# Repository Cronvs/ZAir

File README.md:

DISCLAIMER: The authors of this project are not responsible for how the files are used in any capacity.

CREDIT: This work is directly derivative of the work by [AirGradient](https://www.airgradient.com/)

BUGS: Molex picoblade connector to the "pms5003" is reversed. Cable thus need to be re-crimped, or need to reverse order between sensor and connection.

### ZAir
This work is directly compatible with the [AirGradient ONE](https://www.airgradient.com/indoor/),
it was created in frustration of the size over the monitor,
and personal opinions on LED, including but not limited to screens.

It is indeed a fork of the work done by AirGradient themselves, without whom this project would not have happened.
It was redesigned in KiCAD and has been verified in production via JLCPCB.

All sensors have been integrated directly into the main board, this removes superfluous board ordering or assembly,
however, it also means that "upgrading" with new sensors is harder.
The dimensions have approximately been halved, decreasing the area to around a quarter of the original design.
More could probably be done, but inexperience, and assumptions that the people at AirGradient probably had some good
reason except just temperature made the sensor into the size it is today.

If you like this project consider buying the author(s) a coffee or two.

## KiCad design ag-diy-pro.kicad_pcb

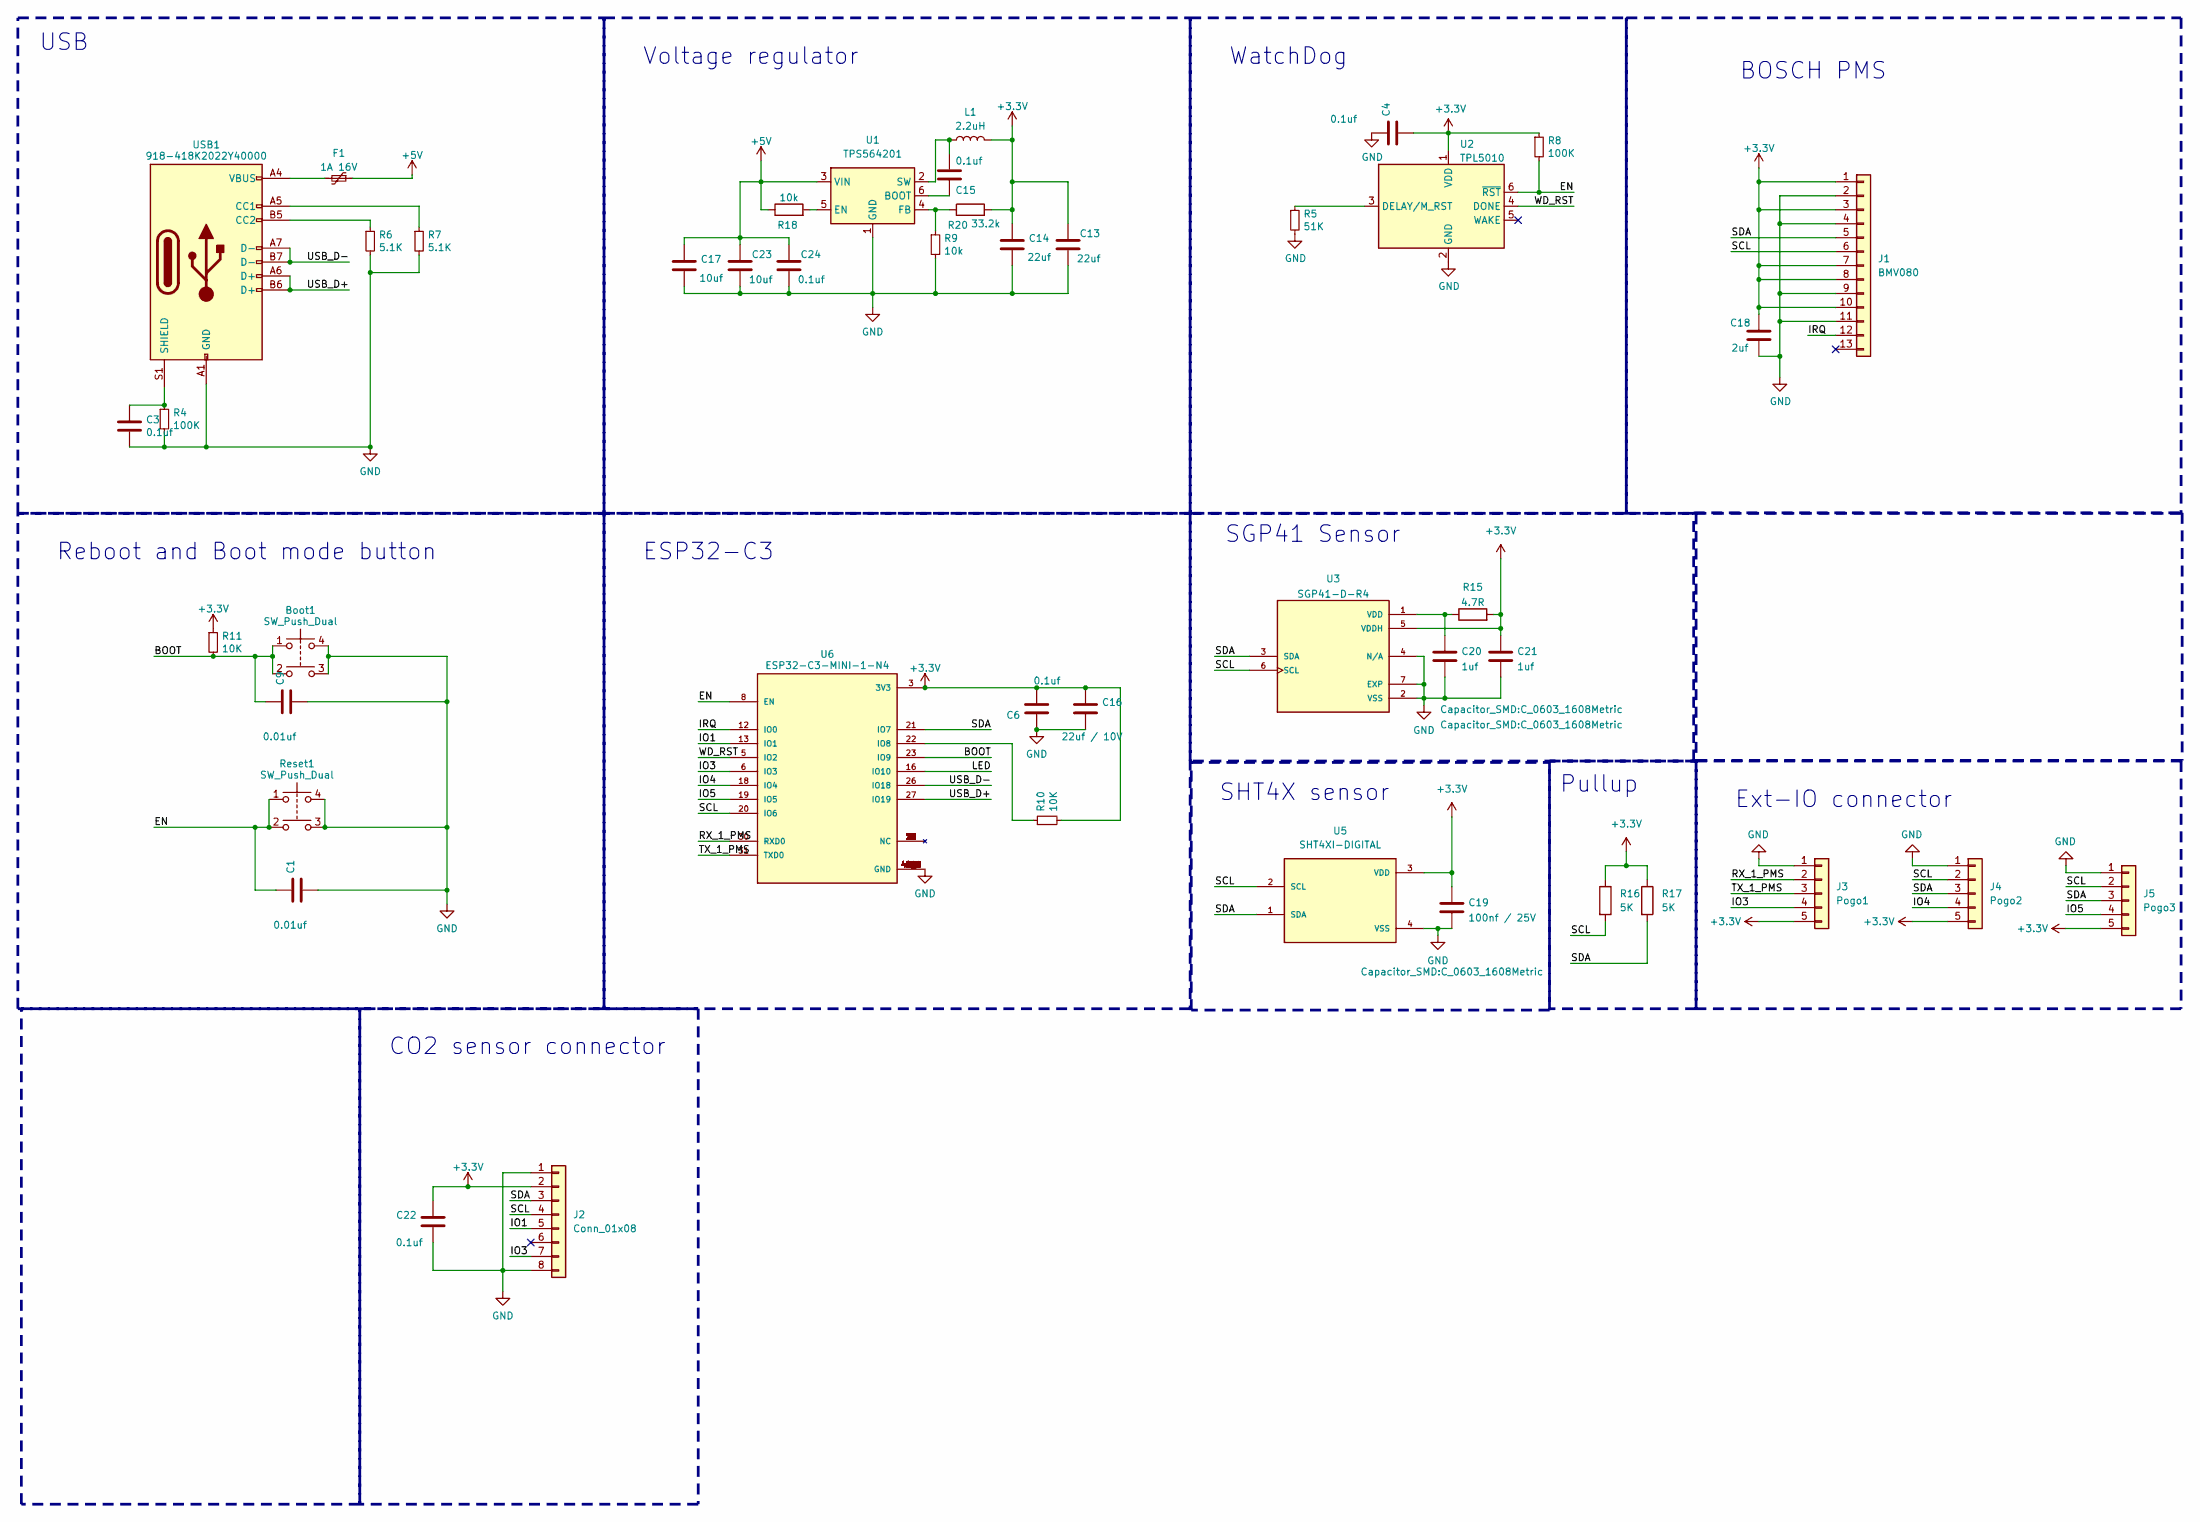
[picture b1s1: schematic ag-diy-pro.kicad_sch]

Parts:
Boot1: SW_Push_Dual; PTS525SM08SMTR2LFS; LCSC Part # C221855
C1, C9: 0.01uf; C_0603_1608Metric; LCSC Part # C1589
C3, C4, C6, C15, C22: 0.1uf; C_0603_1608Metric; LCSC Part # C1590
C13: 22uf; C_0603_1608Metric; LCSC Part # C86295
C14: 22uf; C_0603_1608Metric; LCSC Part # C1590
C16: 22uf / 10V; C_0603_1608Metric; LCSC Part # C86295
C17: 10uf; C_0603_1608Metric; LCSC Part # C1590
C18: 2uf; C_0603_1608Metric; LCSC Part # C86295
C19: 100nf / 25V; C_0603_1608Metric; LCSC Part # C1590
C20, C21: 1uf; C_0603_1608Metric; LCSC Part # C5673
C23: 10uf; C_0603_1608Metric; LCSC Part # C86295
C24: 0.1uf; C_0603_1608Metric; LCSC Part # C86295
F1: 1A 16V; Fuse_1206_3216Metric; LCSC Part # C70075
J1: BMV080; 5035661302
J2: Conn_01x08; S12
J3: Pogo1; PinHeader_1x05_P2.54mm_Vertical
J4: Pogo2; PinHeader_1x05_P2.54mm_Vertical
J5: Pogo3; PinHeader_1x05_P2.54mm_Vertical
L1: 2.2uH; L_0603_1608Metric
R4, R8: 100K; R_0603_1608Metric; LCSC Part # C25803
R5: 51K; R_0603_1608Metric; LCSC Part # C23196
R6, R7: 5.1K; R_0603_1608Metric; LCSC Part # C23186
R9: 10k; R_0603_1608Metric; LCSC Part # C23196
R10, R11: 10K; R_0603_1608Metric; LCSC Part # C25804
R15: 4.7R; R_0603_1608Metric; LCSC Part # C23164
R16, R17: 5K; R_0603_1608Metric; LCSC Part # C166926
R18: 10k; R_0603_1608Metric; LCSC Part # C23164
R20: 33.2k; R_0603_1608Metric; LCSC Part # C23164
Reset1: SW_Push_Dual; PTS525SM08SMTR2LFS; LCSC Part # C221855
U1: TPS564201; SOT-23-6
U2: TPL5010; SOT-23-6; LCSC Part # C473912
U3: SGP41-D-R4; XDCR_SGP41-D-R4; PARTREV 1.0; LCSC Part # C3659325
U5: SHT4XI-DIGITAL; LCSC Part # C9900186997
U6: ESP32-C3-MINI-1-N4; XCVR_ESP32-C3-MINI-1-N4; PARTREV v1.0; LCSC Part # C2934561
USB1: 918-418K2022Y40000; USB_C_Receptacle_Molex_105450-0101; LCSC Part # C168704

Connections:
+3.3V: C4.2, C6.2, C13.1, C14.1, C16.1, C18.1, C19.1, C21.1, C22.1, J1.1, J1.3, J1.7, J1.8, J1.10, J2.2, J3.5, J4.5, J5.5, L1.2, R8.1, R10.2, R11.1, R15.2, R16.1, R17.1, R20.2, U2.1 (VDD), U3.5 (VDDH), U5.3 (VDD), U6.3 (3V3)
+5V: C17.1, C23.1, C24.1, F1.1, R18.1, U1.3 (VIN)
/BOOT: Boot1.1, Boot1.2, C9.1, R11.2, U6.23 (IO9)
/EN: C1.1, R8.2, Reset1.1, Reset1.2, U2.6 (~RST), U6.8 (EN)
/IO1: J2.5, U6.13 (IO1)
/IO3: J2.7, J3.4, U6.6 (IO3)
/IO4: J4.4, U6.18 (IO4)
/IO5: J5.4, U6.19 (IO5)
/IRQ: J1.12, U6.12 (IO0)
/LED: U6.16 (IO10)
/RX_1_PMS: J3.2, U6.30 (RXD0)
/SCL: J1.6, J2.4, J4.2, J5.2, R16.2, U3.6 (SCL), U5.2 (SCL), U6.20 (IO6)
/SDA: J1.5, J2.3, J4.3, J5.3, R17.2, U3.3 (SDA), U5.1 (SDA), U6.21 (IO7)
/TX_1_PMS: J3.3, U6.31 (TXD0)
/USB_D+: U6.27 (IO19), USB1.A6 (D+), USB1.B6 (D+)
/USB_D-: U6.26 (IO18), USB1.A7 (D-), USB1.B7 (D-)
/WD_RST: U2.4 (DONE), U6.5 (IO2)
GND: Boot1.3, Boot1.4, C1.2, C3.2, C4.1, C6.1, C9.2, C13.2, C14.2, C16.2, C17.2, C18.2, C19.2, C20.2, C21.2, C22.2, C23.2, C24.2, J1.2, J1.4, J1.9, J1.11, J2.1, J2.8, J3.1, J4.1, J5.1, R4.2, R5.2, R6.2, R7.2, R9.2, Reset1.3, Reset1.4, U1.1 (GND), U2.2 (GND), U3.2 (VSS), U3.4 (N/A), U3.7 (EXP), U5.4 (VSS), U6.1 (GND), U6.2 (GND), U6.11 (GND), U6.14 (GND), U6.36 (GND), U6.37 (GND), U6.38 (GND), U6.39 (GND), U6.40 (GND), U6.41 (GND), U6.42 (GND), U6.43 (GND), U6.44 (GND), U6.45 (GND), U6.46 (GND), U6.47 (GND), U6.48 (GND), U6.49_1 (GND), U6.49_2 (GND), U6.49_3 (GND), U6.49_4 (GND), U6.49_5 (GND), U6.49_6 (GND), U6.49_7 (GND), U6.49_8 (GND), U6.49_9 (GND), U6.50 (GND), U6.51 (GND), U6.52 (GND), U6.53 (GND), USB1.A1 (GND), USB1.A12 (GND), USB1.B1 (GND), USB1.B12 (GND)
unnamed: F1.2, USB1.A4 (VBUS), USB1.A9 (VBUS), USB1.B4 (VBUS), USB1.B9 (VBUS)
unnamed: C15.2, U1.6 (BOOT)
unnamed: R18.2, U1.5 (EN)
unnamed: R9.1, R20.1, U1.4 (FB)
unnamed: C15.1, L1.1, U1.2 (SW)
unnamed: R5.1, U2.3 (DELAY/M_RST)
unnamed: C20.1, R15.1, U3.1 (VDD)
unnamed: R10.1, U6.22 (IO8)
unnamed: R7.1, USB1.A5 (CC1)
unnamed: R6.1, USB1.B5 (CC2)
unnamed: C3.1, R4.1, USB1.S1 (SHIELD)

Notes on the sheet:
SHT4X sensor
WatchDog
CO2 sensor connector
ESP32-C3
USB
Reboot and Boot mode button
Ext-IO connector
Voltage regulator
BOSCH PMS
SGP41 Sensor
Pullup

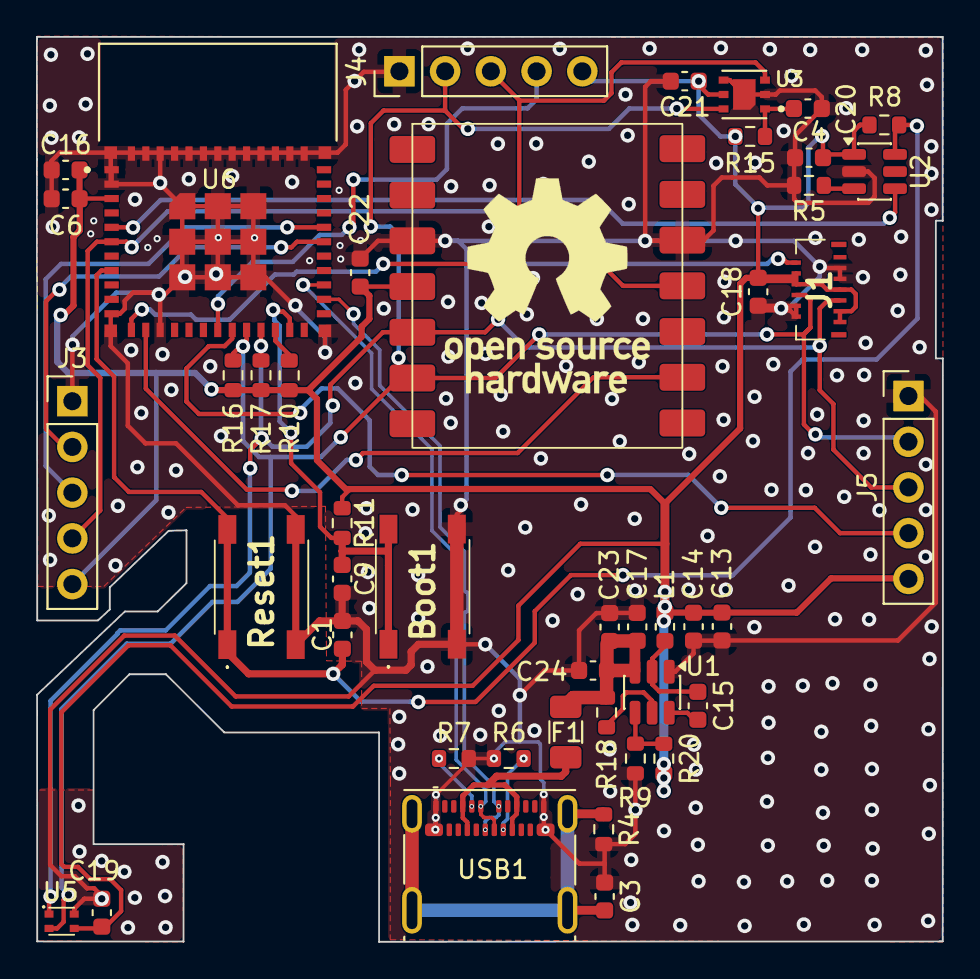
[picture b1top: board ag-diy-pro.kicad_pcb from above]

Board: 2 copper layers, 50.3 x 50.3 mm, 45 parts (0 on the bottom side), 28 nets.

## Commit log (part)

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2025-03-24 init forked
2025-08-03 first working draft and verified build
2025-08-03 init, first revision
2025-11-26 known hardware bug added, nothing critical but need to fix issue in cable domain
2026-01-08 slight change
2026-01-08 added enclosure
